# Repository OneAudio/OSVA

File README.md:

# OSVA 
## Open source versatile analyzer (2 Channels 24 bits 1536 kSPS)

The OSVA project is a 2 channels signal analyzer using high resolution SAR ADC (LTC2380-24).
It has been designed to be used as system analyser but using standard digital audio interface.

The OSVA project include 4 sub-design (boards):
-----------------------------------------------
1. AA2380  - 2 channels ADC board : It is the main board.
2. AA10M08 - CPLD digital board : Optional board
3. AAPSU01 - Low noise SMSP board
4. AACMD01 - Command panel board

 The AA2380 main specifications are :
 ------------------------------------
* 2 ADC Channels using LTC2380-24 (or compatible device)
* 24 bits resolution up to 1536 ksps
* 10Vpp full-scale signal sensitivity (default)
* Single-ended or fully differential mode (switchable)
* 2 analog anti-alias filter cuttoff (38.4kHz/384kHz by default)
* On board ultra low jitter clock
* Direct SPDIF stereo output with support up to 192kHz sampling.
* SinC type Digital filter (x1 to x32 selectable).
* isolated 100MHz External clock input (for sampling synchronisation)
* 2 isolated analog output for coherant sampling capability.
* isolated High speed digital interface to connect :
	- AA10M08 dedicated Digital board
	- USB-Streamer from mini-DSP for 4 channels 24/192k to USB
	- SDR-Widget board for 24/192k I2S to USB

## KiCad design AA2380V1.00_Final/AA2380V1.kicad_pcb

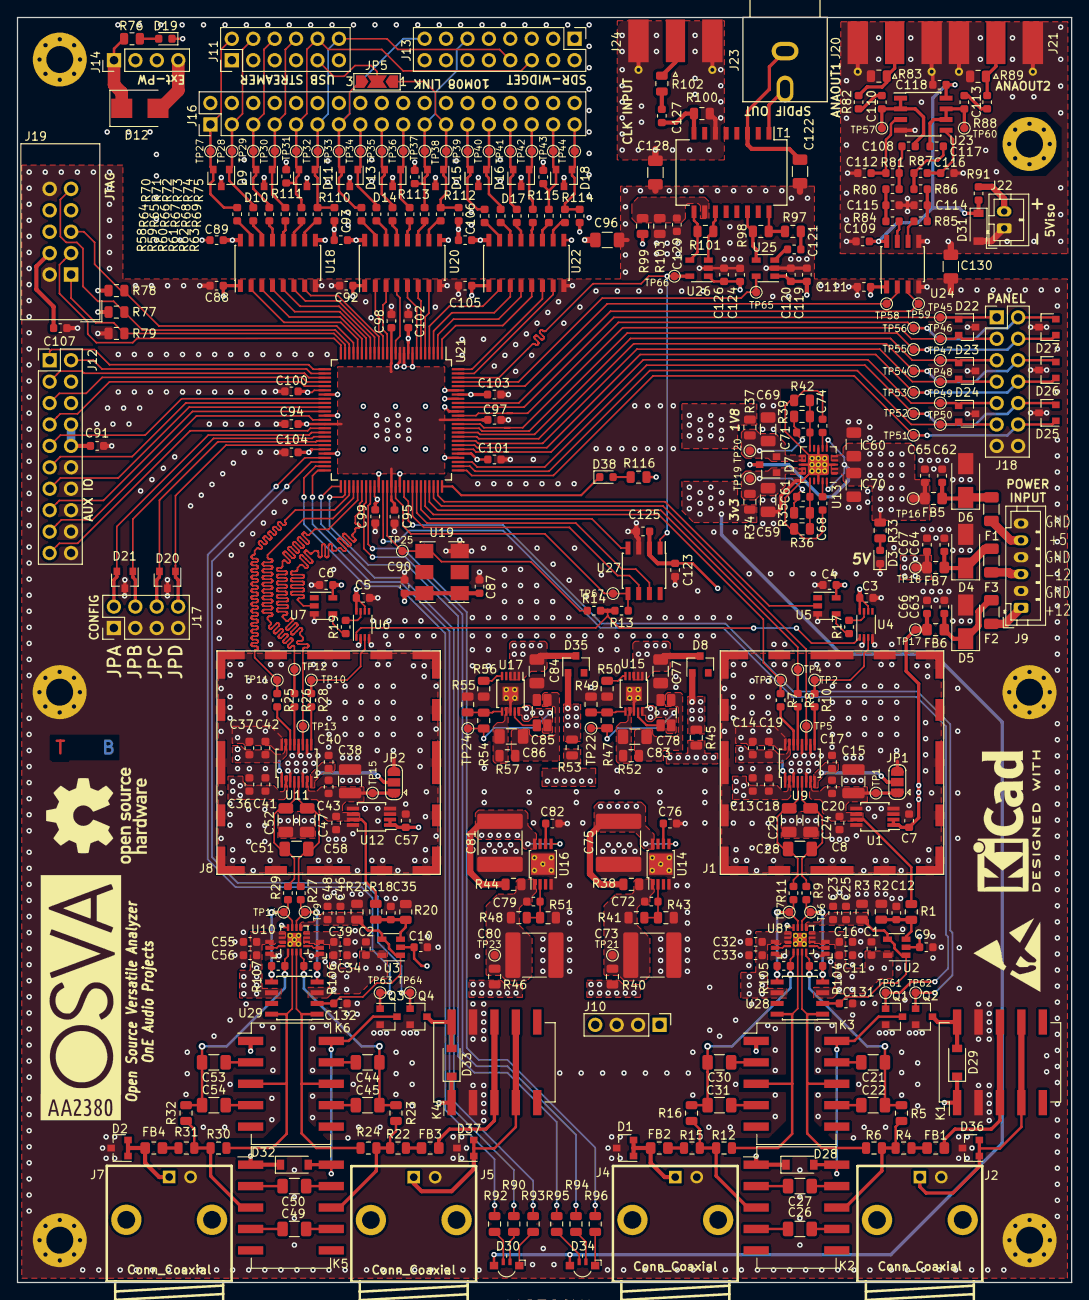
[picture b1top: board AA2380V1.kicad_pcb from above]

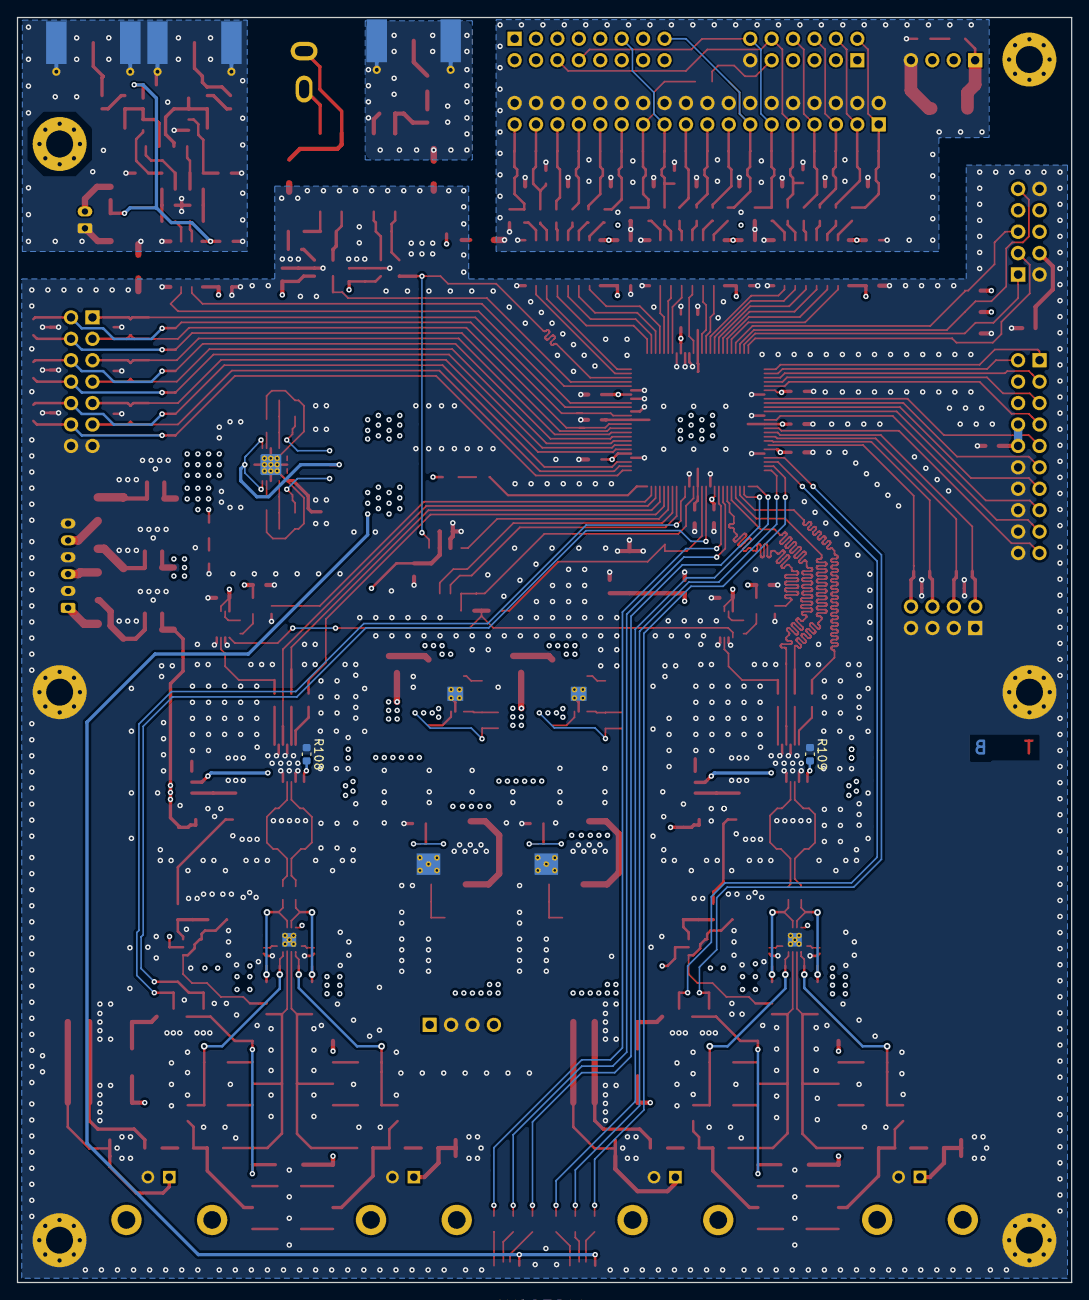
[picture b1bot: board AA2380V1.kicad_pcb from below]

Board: 4 copper layers, 125.0 x 150.0 mm, 435 parts (2 on the bottom side), 272 nets.

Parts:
C1, C2, C3, C4, C5, C6, C7, C9, C10, C16, C17, C18, C19, C20, C25, C32, C39, C40, C41, C42, C43, C48, C55, C57, C88, C89, C90, C91, C92, C93, C94, C95, C97, C100, C101, C102, C103, C105, C106, C109, C111, C118, C119, C124, C125, C127, C129, C131, C132: 100nF/16V; C_0603_1608Metric
C8, C11, C33, C34, C56, C58, C87, C98, C99, C104, C107, C123: 2.2uF/16V; C_0603_1608Metric
C12, C13, C14, C23, C35, C36, C37, C46: 10uF/6.3V; C_0603_1608Metric
C15, C38: 47uF/6.3V; C_1210_3225Metric
C21, C30, C44, C53: 2.7nF/100V COG; C_1206_3216Metric
C22, C31, C45, C54: 270pF/100V COG; C_1206_3216Metric
C24, C29, C47, C52: 6.8nF/100V COG; C_1206_3216Metric
C26, C49: 390pF/100V COG; C_1206_3216Metric
C27, C50: 3.9nF/100V COG; C_1206_3216Metric
C28, C51: 3.3nF/100V COG; C_1206_3216Metric
C59, C60, C69, C70, C77, C84: 22uF/16V X7R; C_1206_3216Metric
C61, C71, C72, C76, C79, C82, C120, C126: 10nF/25V X7R; C_0603_1608Metric
C62, C63, C64, C65, C66, C67, C68, C74, C110, C113: 1uF/25V X7R; C_0603_1608Metric
C73, C75, C80, C81: 22uF/25V X7R; C_2220_5650Metric
C78, C85: 22uF/16V X7R; C_1206_3216Metric_4-PADS
C83, C86: 22uF/6v3; C_1206_3216Metric
C96, C122, C128, C130: 1nF/500V X7R; C_1206_3216Metric
C108, C117: 10nF 1%; C_0603_1608Metric
C112, C116: 2.7nF 1%; C_0603_1608Metric
C114, C115: 1nF 1%; C_0603_1608Metric
C121: 2u2/16V; C_0603_1608Metric
D1, D2, D36, D37: SZNUP2105L; SOT-23
D3, D19, D38: LED_Small_ALT; LED_0603_1608Metric
D4, D5: P4SMA16A; D_SMA
D6: P4SMA6.8A; D_SMA
D7: BAT54C; SOT-23
D8, D35: BAV99; SOT-23
D9, D10, D11, D13, D14, D15, D16, D17, D18, D20, D21, D22, D23, D24, D25, D26, D27: PESD5V0X1BT; SOT-23
D12: SMLVT3V3_0; D_SMB
D28, D29, D31, D32, D33: MBR0540; D_SOD-123
D30, D34: APFA3010; LED_Kingbright_APFA3010_3x1.5mm_Horizontal
F1: 500mA; Fuse_1206_3216Metric
F2, F3: 200mA; Fuse_1206_3216Metric
FB1, FB2, FB3, FB4: 600R@100M; L_0805_2012Metric_Pad1.15x1.40mm_HandSolder
FB5, FB6, FB7: 600/100M; L_0805_2012Metric_Pad1.15x1.40mm_HandSolder
H1, H2, H3, H4, H5, H6: MountingHole_Pad; MountingHole_3.2mm_M3_Pad_Via
J1, J8: RF_Shield_Two_Pieces; wurth-shield
J2, J4, J5, J7: Conn_Coaxial; BNC_90_73137-5003
J9: Conn_01x06_Male; JST_PH_B6B-PH-K_1x06_P2.00mm_Vertical
J10: Conn_01x04_Female; PinHeader_1x04_P2.54mm_Vertical
J11: Conn_02x06_Odd_Even; PinHeader_2x06_P2.54mm_Vertical
J12: Conn_02x10_Odd_Even; PinHeader_2x10_P2.54mm_Vertical
J13: Conn_02x08_Odd_Even; PinHeader_2x08_P2.54mm_Vertical
J14: Conn_01x04; PinHeader_1x04_P2.54mm_Vertical
J16: Conn_02x18_Odd_Even; PinHeader_2x18_P2.54mm_Vertical
J17: Conn_02x04_Odd_Even; PinHeader_2x04_P2.54mm_Vertical
J18: Conn_02x07_Odd_Even; PinHeader_2x07_P2.54mm_Vertical
J19: Conn_02x05_Odd_Even; IDC-Header_2x05_P2.54mm_Vertical
J20, J21, J24: Conn_Coaxial; SMA_Molex_73251-1153_EdgeMount_Horizontal
J22: Conn_02x01; JST_PH_B2B-PH-K_1x02_P2.00mm_Vertical
J23: Conn_Coaxial; RCA
JP1, JP2: SolderJumper_3_Bridged12; SolderJumper-3_P1.3mm_Open_RoundedPad1.0x1.5mm
JP3, JP4, JP6, JP7: SolderJumper_3_Open; SolderJumper-3_P0.7mm_Open_Pad0.5x1mm_NumberLabels
JP5: SolderJumper_3_Open; SolderJumper-3_P2.0mm_Open_TrianglePad1.0x1.5mm_NumberLabels
K1, K2, K3, K4, K5, K6: RELAY_DPDT; Relay_DPDT_Omron_G6H-2F
Q1, Q2, Q3, Q4: BSS138; SOT-23
R1, R2, R18, R20, R79: 1k; R_0805_2012Metric
R3, R21: 249; R_0805_2012Metric
R4, R5, R15, R16, R22, R23, R31, R32: 1k 0.5%; R_0805_2012Metric
R6, R12, R24, R30: 549 0.5%; R_0805_2012Metric
R7, R8, R10, R13, R14, R17, R19, R25, R26, R28, R58, R59, R60, R61, R62, R63, R64, R65, R66, R67, R68, R69, R70, R71, R72, R73, R74, R75: 33; R_0603_1608Metric
R9, R11, R27, R29, R91: 10; R_0603_1608Metric
R33: 2K2; R_0805_2012Metric
R34, R37, R38, R40, R44, R45, R46, R53, R100: NP; R_0805_2012Metric
R35: 33k2; R_0805_2012Metric
R36: 10k7; R_0805_2012Metric
R39: 13k7; R_0805_2012Metric
R41, R48: 32k4; R_0805_2012Metric
R42: 11k; R_0805_2012Metric
R43, R49, R51, R55, R77, R78: 10k; R_0805_2012Metric
R47: 93.1k; R_0805_2012Metric
R50, R56: 2.55k; R_0805_2012Metric
R52: 33.2k; R_0805_2012Metric
R54: 68.1k; R_0805_2012Metric
R57: 24.9k; R_0805_2012Metric
R76: 1k5; R_0805_2012Metric
R80, R86: 2.61k; R_0603_1608Metric
R81, R87: 3.24k; R_0603_1608Metric
R82, R88: 2k; R_0603_1608Metric
R83, R89: 49.9; R_0805_2012Metric
R84, R85: 200; R_0603_1608Metric
R90, R92, R93, R94, R95, R96: 330; R_0805_2012Metric
R97: 243; R_0805_2012Metric
R98: 107; R_0805_2012Metric
R99, R103: 150; R_0805_2012Metric
R101: 75; R_0805_2012Metric
R102: 0; R_0805_2012Metric
R104, R105, R106, R107: 0; R_0603_1608Metric
R108, R109: 1k; R_0603_1608Metric
R110, R111, R112, R113, R114, R115: 10k; R_0603_1608Metric
R116: 2k2; R_0805_2012Metric
T1: 749010310; SOIC-16W_7.5x12.8mm_P1.27mm
TP1, TP2, TP3, TP4, TP5, TP6, TP7, TP9, TP10, TP11, TP12, TP13, TP14, TP15, TP16, TP17, TP18, TP19, TP20, TP21, TP22, TP23, TP24, TP25, TP27, TP28, TP29, TP30, TP31, TP32, TP33, TP34, TP35, TP36, TP37, TP38, TP39, TP40, TP41, TP42, TP43, TP44, TP45, TP46, TP47, TP48, TP49, TP50, TP51, TP52, TP53, TP54, TP55, TP56, TP57, TP58, TP59, TP60, TP61, TP62, TP63, TP64, TP65, TP66, TP67: TestPoint; TestPoint_Pad_D1.0mm
U1, U12: LTC6655CHMS8-5; MSOP-8_3x3mm_P0.65mm
U2, U3: LT6202CS5; SOT-23-5
U4, U6: NL17SZ74; VSSOP-8_2.3x2mm_P0.5mm
U5, U7: NC7SZ04M5X; SOT-23-5
U8, U10: ADA4945-1; LFCSP-16-1EP_3x3mm_P0.5mm_EP1.65x1.65mmThermalviax5_0.3mm
U9, U11: LTC2380CMS-24; MSOP-16_3x4mm_P0.5mm
U13: TPS7A8701RT; QFN-20-1EP_4x4mm_P0.5mm_EP2.5x2.5mm_ThermalViasx9_0.3mm
U14: TPS7A4901DGN; MSOP-8-1EP_3x3mm_P0.65mm_EP2.54x2.8mm_ThermalViasx5_0.3mm
U15, U17: LT3042IMSE; MSOP-10-1EP_3x3mm_P0.5mm_EP1.68x1.88mmThermalviax4_0.3mm
U16: TPS7A3001DG; MSOP-8-1EP_3x3mm_P0.65mm_EP2.54x2.8mm_ThermalViasx5_0.3mm
U18, U20, U22: Si8662BB-B-IS1; SOIC-16_3.9x9.9mm_P1.27mm
U19: Si545CAA100M000A; Oscillator_SMD_5x7_Si545
U21: 5M570ZT100C5N; LQFP-100_14x14mm_P0.5mm
U23: LT6203CS8; SOIC-8_3.9x4.9mm_P1.27mm
U24: SI8620BB-B-IS; SOIC-8_3.9x4.9mm_P1.27mm
U25: DS90LV011A; SOT-23-5
U26: DS90LV012A; SOT-23-5
U27: NB3N511; SOIC-8_3.9x4.9mm_P1.27mm
U28, U29: OPA1632D; SOIC-8_3.9x4.9mm_P1.27mm

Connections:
3V3in: C89.2, C93.2, C106.2, D12.1, J14.1, R76.2, U18.16, U20.16, U22.16
+1V8: C94.2, C95.2, C97.2, C98.1, R37.1, U21.13, U21.39, U21.63, U21.88
+2V5: C13.2, C18.1, C36.2, C41.1, R53.1, U9.2, U11.2
+3.3VA: C3.2, C4.2, C5.2, C6.2, C14.2, C19.1, C37.2, C42.1, C87.2, C90.1, C123.2, C125.1, R45.1, U4.6, U4.8, U5.5, U6.6, U6.8, U7.5, U9.15, U11.15, U19.1, U19.6, U27.2
+3V3: C88.1, C91.2, C92.1, C99.1, C100.2, C101.2, C102.2, C103.2, C104.1, C105.1, C107.1, C111.1, C119.1, C120.1, C124.1, C126.1, D30.2, D34.2, J12.8, J12.10, J19.4, R34.1, R77.1, R78.1, R99.1, R116.2, U18.1, U20.1, U21.9, U21.31, U21.45, U21.59, U21.80, U21.94, U22.1, U24.1, U25.1, U26.1
+5V: C60.1, C65.1, C70.1, C77.1, C84.1, D7.3, D8.3, D28.1, D29.1, D32.1, D33.1, D35.3, FB5.2, K1.1, K2.1, K3.1, K4.1, K5.1, K6.1, R33.1, TP16.1, U13.1, U13.2, U13.4, U13.5, U13.6, U13.20, U15.1, U15.2, U15.3, U17.1, U17.2, U17.3
+12VA: C7.1, C57.1, C66.1, C75.2, FB6.2, R38.2, TP17.1, U1.1, U1.2, U12.1, U12.2, U14.5, U14.8
-12VA: C67.1, C81.2, FB7.2, R44.2, TP18.1, U16.5, U16.8
/Analog front end/FB1+: C21.1, C22.1, R5.1, R104.2, U8.4
/Analog front end/FB1-: C30.1, C31.1, R16.1, R105.2, U8.1
/Analog front end/FB2+: C44.1, C45.1, R23.1, R106.2, U10.4
/Analog front end/FB2-: C53.1, C54.1, R32.1, R107.2, U10.1
/Analog front end/IN1+: K3.3, R12.2, U8.2, U28.8
/Analog front end/IN1-: K3.8, R6.2, U8.3, U28.1
/Analog front end/IN2+: K6.3, R30.2, U10.2, U29.8
/Analog front end/IN2-: K6.8, R24.2, U10.3, U29.1
/Analog front end/OUTN1: R11.1, R105.1, TP7.1, U8.11, U28.5
/Analog front end/OUTN2: R29.1, R107.1, TP14.1, U10.11, U29.5
/Analog front end/OUTP1: R9.2, R104.1, TP6.1, U8.10, U28.4
/Analog front end/OUTP2: R27.2, R106.1, TP9.1, U10.10, U29.4
/Analog front end/REF+5CH1: C8.1, C15.2, C20.2, JP1.1, R1.2, TP1.1, U1.6, U1.7, U9.7
/Analog front end/REF+5CH2: C38.2, C43.2, C58.1, JP2.1, R18.2, TP15.1, U11.7, U12.6, U12.7
/Analog front end/VOCM1: C23.1, C25.2, C131.2, R3.2, U2.1, U2.4, U8.9, U28.2
/Analog front end/VOCM2: C46.1, C48.2, C132.2, R21.2, U3.1, U3.4, U10.9, U29.2
ADC1_BUSY: TP5.1, U9.11, U21.73
ADC1_CNV: U5.2, U21.74
ADC1_SCK: R8.1, TP4.1, U21.72
ADC1_SDO: R7.1, TP3.1, U21.71
ADC2_BUSY: TP13.1, U11.11, U21.55
ADC2_CNV: U7.2, U21.56
ADC2_SCK: R26.1, TP12.1, U21.54
ADC2_SDO: R25.1, TP11.1, U21.53
CLK100M: R14.1, TP25.1, U19.4, U21.62
CLKEXT: TP66.1, U21.98, U26.5, U27.1
CLKIN_xN: R13.1, TP67.1, U21.64, U27.5
CONF0: D21.2, J17.2, U21.41
CONF1: D21.1, J17.4, U21.42
CONF2: D20.2, J17.6, U21.43
CONF3: D20.1, J17.8, U21.44
FILTER_CH1: Q1.1, TP61.1, U21.61
FILTER_CH2: Q3.1, TP63.1, U21.47
GND: C1.1, C2.1, C3.1, C4.1, C5.1, C6.1, C7.2, C8.2, C9.1, C10.1, C11.1, C12.2, C13.1, C14.1, C15.1, C16.1, C17.1, C18.2, C19.2, C20.1, C23.2, C24.1, C25.1, C29.2, C32.1, C33.1, C34.1, C35.2, C36.1, C37.1, C38.1, C39.1, C40.1, C41.2, C42.2, C43.1, C46.2, C47.1, C48.1, C52.2, C55.1, C56.1, C57.2, C58.2, C59.2, C60.2, C62.2, C63.2, C64.2, C65.2, C66.2, C67.2, C68.2, C69.2, C70.2, C73.1, C74.2, C75.1, C76.1, C77.2, C78.3, C80.1, C81.1, C82.1, C84.2, C85.3, C87.1, C88.2, C90.2, C91.1, C92.2, C94.1, C95.1, C96.1, C97.1, C98.2, C99.2, C100.1, C101.1, C102.1, C103.1, C104.2, C105.2, C107.2, C111.2, C119.2, C120.2, C122.1, C123.1, C124.2, C125.2, C126.2, C128.1, C129.1, C130.1, C131.1, C132.1, D1.3, D2.3, D3.1, D4.2, D5.2, D6.2, D20.3, D21.3, D22.3, D23.3, D24.3, D25.3, D26.3, D27.3, D36.3, D37.3, H1.1, H2.1, H4.1, H5.1, J1.1, J2.2, J4.2, J5.2, J7.2, J8.1, J9.2, J9.4, J9.6, J10.2, J10.3, J12.12, J12.14, J12.16, J12.18, J12.20, J17.1, J17.3, J17.5, J17.7, J18.13, J18.14, J19.2, J19.10, JP1.3, JP2.3, JP3.1, JP4.1, JP6.1, JP7.1, K1.2, K1.9, K4.2, K4.9, Q1.2, Q2.2, Q3.2, Q4.2, R2.1, R3.1, R20.1, R21.1, R36.2, R42.2, R43.2, R49.2, R50.2, R51.2, R55.2, R56.2, R79.2, R103.2, R108.1, R109.1, U1.3, U1.4, U1.5, U1.8, U4.2, U4.4, U5.3, U6.2, U6.4, U7.3, U8.17, U9.3, U9.6, U9.10, U9.12, U9.16, U10.17, U11.3, U11.6, U11.10, U11.12, U11.16, U12.3, U12.4, U12.5, U12.8, U13.3, U13.8, U13.13, U13.18, U13.21, U14.4, U14.9, U15.8, U15.11, U16.4, U16.9, U17.8, U17.11, U18.8, U19.3, U20.8, U21.8, U21.10, U21.11, U21.32, U21.37, U21.46, U21.60, U21.65, U21.79, U21.90, U21.93, U21.95, U22.8, U24.4, U25.2, U26.2, U27.3
GNDD: C89.1, C93.1, C96.2, C106.1, D9.3, D10.3, D11.3, D12.2, D13.3, D14.3, D15.3, D16.3, D17.3, D18.3, D19.1, J11.11, J14.4, J16.2, J16.4, J16.6, J16.8, J16.10, J16.12, J16.14, J16.16, J16.18, J16.20, J16.22, J16.24, J16.26, J16.28, J16.30, J16.32, J16.34, J16.36, R110.2, R111.2, R112.2, R113.2, R114.2, R115.2, U18.9, U20.9, U22.9
GNDS: C109.1, C112.1, C114.1, C115.1, C116.1, C118.1, C130.2, D31.2, J20.2, J21.2, J22.1, R83.2, R89.2, U23.4, U24.5
IN_PIN0: U18.6, U21.17
IN_PIN1: U18.7, U21.16
IN_PIN2: U20.6, U21.6
IN_PIN3: U20.7, U21.5
IN_PIN4: U21.100, U22.6
IN_PIN5: U21.99, U22.7
ISIN_PIN0: D11.2, J11.10, J13.6, J16.9, R62.2, R111.1, TP31.1
ISIN_PIN1: D11.1, J11.12, J13.8, J16.11, R63.2, R110.1, TP32.1
ISIN_PIN2: D15.2, J13.11, J14.3, J16.21, R68.2, R113.1, TP37.1
ISIN_PIN3: D15.1, J16.23, JP5.1, R69.2, R112.1, TP38.1
ISIN_PIN4: D18.2, J16.33, R74.2, R115.1, TP43.1
ISIN_PIN5: D18.1, J16.35, R75.2, R114.1, TP44.1
ISOUT_PIN0: D9.2, J11.2, J13.1, J16.1, R58.2, TP27.1
ISOUT_PIN1: D9.1, J11.4, J13.3, J16.3, R59.2, TP28.1
ISOUT_PIN2: D10.2, J11.6, J13.5, J16.5, R60.2, TP29.1
ISOUT_PIN3: D10.1, J11.8, J13.13, J16.7, R61.2, TP30.1
ISOUT_PIN4: D13.2, J13.15, J16.13, JP5.3, R64.2, TP33.1
ISOUT_PIN5: D13.1, J13.2, J16.15, R65.2, TP34.1
ISOUT_PIN6: D14.2, J16.17, R66.2, TP35.1
ISOUT_PIN7: D14.1, J16.19, R67.2, TP36.1
ISOUT_PIN8: D16.2, J16.25, R70.2, TP39.1
ISOUT_PIN9: D16.1, J16.27, R71.2, TP40.1
ISOUT_PIN10: D17.2, J16.29, R72.2, TP41.1
ISOUT_PIN11: D17.1, J16.31, R73.2, TP42.1
JTAG_TCK: J19.1, R79.1, U21.24
JTAG_TDI: J19.9, R77.2, U21.23
JTAG_TDO: J19.3, U21.25
JTAG_TMS: J19.5, R78.2, U21.22
LED1_G: R92.1, U21.49
LED1_R: R93.1, U21.51
LED1_Y: R90.1, U21.50
LED2_G: R95.1, U21.52
LED2_R: R96.1, U21.58
LED2_Y: R94.1, U21.57
LED48k: D23.2, J18.7, TP48.1, U21.83
LED96k: D24.1, J18.9, TP49.1, U21.81
LED192k: D24.2, J18.11, TP50.1, U21.77
LED_CAL: D25.2, J18.10, TP52.1, U21.78
LED_SE: D25.1, J18.12, TP51.1, U21.76
LED_filtoff: D26.1, J18.8, TP53.1, U21.82
LEDavg0: D27.2, J18.2, TP56.1, U21.89
LEDavg1: D27.1, J18.4, TP55.1, U21.86
LEDavg2: D26.2, J18.6, TP54.1, U21.84
unnamed: C12.1, R1.1, R2.2, U2.3
unnamed: C17.2, JP1.2, U9.8
unnamed: C21.2, K3.9
unnamed: C22.2, K3.7
unnamed: C24.2, C28.2, R9.1, U9.5
unnamed: C26.1, K2.7
unnamed: C26.2, K2.4
unnamed: C27.1, K2.9
unnamed: C27.2, K2.2
unnamed: C28.1, C29.1, R11.2, U9.4
unnamed: C30.2, K3.2
unnamed: C31.2, K3.4
unnamed: C35.1, R18.1, R20.2, U3.3
unnamed: C40.2, JP2.2, U11.8
unnamed: C44.2, K6.9
unnamed: C45.2, K6.7
unnamed: C47.2, C51.2, R27.1, U11.5
unnamed: C49.1, K5.4
unnamed: C49.2, K5.7
unnamed: C50.1, K5.2
unnamed: C50.2, K5.9
unnamed: C51.1, C52.1, R29.2, U11.4
unnamed: C53.2, K6.2
unnamed: C54.2, K6.4
unnamed: C59.1, C61.2, D7.1, R34.2, R35.1, TP19.1, U13.14, U13.15
unnamed: C61.1, R35.2, R36.1, U13.16
unnamed: C62.1, D6.1, F1.1, FB5.1
unnamed: C63.1, D5.1, F2.1, FB6.1
unnamed: C64.1, D4.1, F3.1, FB7.1
unnamed: C68.1, U13.19
unnamed: C69.1, C71.2, D7.2, R37.2, R39.1, TP20.1, U13.11, U13.12
unnamed: C71.1, R39.2, R42.1, U13.10
unnamed: C72.1, R41.2, R43.1, U14.2
unnamed: C72.2, C73.2, R38.1, R40.2, R41.1, TP21.1, U14.1
unnamed: C74.1, U13.7
unnamed: C76.2, U14.6
unnamed: C78.1, D8.1, R45.2, R47.1, TP22.1, U15.10
unnamed: C78.2, U15.9
unnamed: C78.4, C83.2, R52.2
unnamed: C79.1, R48.2, R51.1, U16.2
unnamed: C79.2, C80.2, R44.1, R46.2, R48.1, TP23.1, U16.1
unnamed: C82.2, U16.6
unnamed: C83.1, R52.1, U15.7
unnamed: C85.1, D35.1, R53.2, R54.1, TP24.1, U17.10
unnamed: C85.2, U17.9
unnamed: C85.4, C86.2, R57.2
unnamed: C86.1, R57.1, U17.7
unnamed: C108.1, C110.2, TP57.1, U23.1, U23.2
unnamed: C108.2, R80.2, R81.1
unnamed: C110.1, R82.1
unnamed: C112.2, R81.2, U23.3
unnamed: C113.1, R88.1
unnamed: C113.2, C117.1, TP60.1, U23.6, U23.7
unnamed: C114.2, R85.2, R86.1
unnamed: C115.2, R80.1, R84.2
unnamed: C116.2, R87.2, U23.5
unnamed: C117.2, R86.2, R87.1
unnamed: C121.1, R97.1
unnamed: C121.2, U25.3
unnamed: C122.2, J23.2, T1.3
unnamed: C127.1, R102.1
unnamed: C127.2, R100.1, T1.8
unnamed: C128.2, J24.2, R100.2, T1.6
unnamed: C129.2, R99.2, R103.1, T1.10
unnamed: D1.1, D1.2, FB2.1, J4.1
unnamed: D2.1, D2.2, FB4.1, J7.1
unnamed: D3.2, R33.2
unnamed: D19.2, R76.1
unnamed: D28.2, K2.10, K3.10, Q1.3
unnamed: D29.2, K1.10, Q2.3
unnamed: D30.1, R93.2
unnamed: D30.3, R92.2
unnamed: D30.4, R90.2
unnamed: D32.2, K5.10, K6.10, Q3.3
unnamed: D33.2, K4.10, Q4.3
unnamed: D34.1, R96.2
unnamed: D34.3, R95.2
unnamed: D34.4, R94.2
unnamed: D36.1, D36.2, J2.1, K1.4, K1.7
unnamed: D37.1, D37.2, J5.1, K4.4, K4.7
unnamed: D38.1, U21.75
unnamed: D38.2, R116.1
unnamed: F1.2, J9.5
unnamed: F2.2, J9.1
unnamed: F3.2, J9.3
unnamed: FB1.1, R4.2
unnamed: FB1.2, K1.3, K1.8
unnamed: FB2.2, R15.2
unnamed: FB3.1, R22.2
unnamed: FB3.2, K4.3, K4.8
unnamed: FB4.2, R31.2
unnamed: J11.9, JP5.2
unnamed: J20.1, R82.2, R83.1
unnamed: J21.1, R88.2, R89.1
unnamed: J22.2, R91.2
unnamed: J23.1, T1.1
unnamed: J24.1, R102.2
unnamed: JP3.2, U8.5
unnamed: JP4.2, U8.16
unnamed: JP6.2, U10.5
unnamed: JP7.2, U10.16
unnamed: K2.3, R12.1, R15.1, R16.2
unnamed: K2.8, R4.1, R5.2, R6.1
unnamed: K5.3, R30.1, R31.1, R32.2
unnamed: K5.8, R22.1, R23.2, R24.1
unnamed: R7.2, U9.14
unnamed: R8.2, U9.13
unnamed: R10.1, TP2.1, U4.3
unnamed: R10.2, U9.9
unnamed: R13.2, R14.2, U4.1, U6.1
unnamed: R17.1, U5.4
unnamed: R17.2, U4.7
unnamed: R19.1, U7.4
unnamed: R19.2, U6.7
unnamed: R25.2, U11.14
unnamed: R26.2, U11.13
unnamed: R28.1, TP10.1, U6.3
unnamed: R28.2, U11.9
unnamed: R47.2, R49.1, U15.6
unnamed: R50.1, U15.5
unnamed: R54.2, R55.1, U17.6
unnamed: R56.1, U17.5
unnamed: R58.1, U18.15
unnamed: R59.1, U18.14
unnamed: R60.1, U18.13
unnamed: R61.1, U18.12
unnamed: R62.1, U18.11
unnamed: R63.1, U18.10
unnamed: R64.1, U20.15
unnamed: R65.1, U20.14
unnamed: R66.1, U20.13
unnamed: R67.1, U20.12
unnamed: R68.1, U20.11
unnamed: R69.1, U20.10
unnamed: R70.1, U22.15
unnamed: R71.1, U22.14
unnamed: R72.1, U22.13
unnamed: R73.1, U22.12
unnamed: R74.1, U22.11
unnamed: R75.1, U22.10
unnamed: R84.1, U24.7
unnamed: R85.1, U24.6
unnamed: R97.2, R98.1, T1.16
unnamed: R98.2, T1.14, U25.4
unnamed: R101.1, T1.9, U26.4
unnamed: R101.2, T1.11, U26.3
unnamed: R108.2, U9.1
unnamed: R109.2, U11.1
OUT_PIN0: U18.2, U21.21
OUT_PIN1: U18.3, U21.20
OUT_PIN2: U18.4, U21.19
OUT_PIN3: U18.5, U21.18
OUT_PIN4: U20.2, U21.15
OUT_PIN5: U20.3, U21.14
OUT_PIN6: U20.4, U21.12
OUT_PIN7: U20.5, U21.7
OUT_PIN8: U21.4, U22.2
OUT_PIN9: U21.3, U22.3
OUT_PIN10: U21.2, U22.4
OUT_PIN11: U21.1, U22.5
PLLS0: U21.68, U27.6
PLLS1: U21.70, U27.4
PLL_OE: U21.69, U27.7
PWM0: TP58.1, U21.96, U24.2
PWM1: TP59.1, U21.92, U24.3
ROT_Push: D23.1, J18.5, TP47.1, U21.85
ROT_Ta: D22.1, J18.1, TP45.1, U21.91
ROT_Tb: D22.2, J18.3, TP46.1, U21.87
SE_CH1: Q2.1, TP62.1, U21.66
SE_CH2: Q4.1, TP64.1, U21.48
SPDIFO: TP65.1, U21.97, U25.5
UIO_00: J12.1, U21.26
UIO_01: J12.3, U21.28
UIO_02: J12.5, U21.29
UIO_03: J12.7, U21.30
UIO_04: J12.9, U21.33
UIO_05: J12.11, U21.34
UIO_06: J12.13, U21.35
UIO_07: J12.15, U21.36
UIO_08: J12.17, U21.38
UIO_09: J12.19, U21.40
UIO_10: J12.2, U21.27
VAA: C1.2, C2.2, C11.2, C16.2, C34.2, C39.2, J10.1, JP3.3, JP6.3, R40.1, U2.5, U3.5, U8.6, U8.7, U8.8, U8.12, U10.6, U10.7, U10.8, U10.12, U28.3, U29.3
VCC: C109.2, C118.2, D31.1, R91.1, U23.8, U24.8
VEE: C9.2, C10.2, C32.2, C33.2, C55.2, C56.2, J10.4, JP4.3, JP7.3, R46.1, U2.2, U3.2, U8.13, U8.14, U8.15, U10.13, U10.14, U10.15, U28.6, U29.6

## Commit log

2019-03-08 AA2380v1.00 - Initial commit
